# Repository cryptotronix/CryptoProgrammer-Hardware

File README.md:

# Crypto Programmer Hardware

This repo is the hardware files for the Crypto Programmer, a tool that
is hopefully useful for working with the Microchip
CryptoAuthentication Line.

Microchip already makes a useful development git
(https://www.microchip.com/developmenttools/productdetails.aspx?partno=at88ck101sk-mah-xpro),
and the schematics and firmware, but we wanted to "Build our own
Birdfeeder." The intention for this project is to fully Open Source
Hardware, although it doesn't quite meet the definition:
https://www.oshwa.org/definition/

## Overview

The intention of this tool is to expose a scripting-like interface on
a USB-Host that can send the raw byte commands to the part over
I2C. In other words, it is an USB-to-I2C bridge. Most dedicated
USB-to-I2C bridge have a hard-stop of a reasonable number of
bytes. The CryptoAuthentication parts however, send commands in the
few hundred bytes in a continuous I2C frame. Hence, why this tool
exists.

The other use-case for this tool is that you could program the MCU and
then use it to program other CryptoAuthentication parts with the use
of the "extra special button." I often lift CryptoAuthentication parts
from PCBs, drop them in a socket and dump their memory and this tool
should make that easier for me as well.

## Hardware Required

You'll want to attach the USB micro cable to the Crypto Programmer
then attach the plug-side to an appropriate port. I2C lines are on the
right-angle header and you can fly-wire to your heart's content, but
your life will be much easier if you get yourself the AT88CK101 Kit
(https://www.microchip.com/developmenttools/productdetails.aspx?partno=at88ck101sk-mah-xpro)
which comes with a UDFN or SOIC8 socket. The right angle header will
mate with the socket board. This will allow you to test your code
against the Microchip tools, use the CryptoProgammer, and then attach
it to a Microchip development board like a SAMV71.

## Status

Rev A of the Hardware is done and works (we think). We are still
working on the firmware, so once that's in a workable state that will
be released under a BSD license.

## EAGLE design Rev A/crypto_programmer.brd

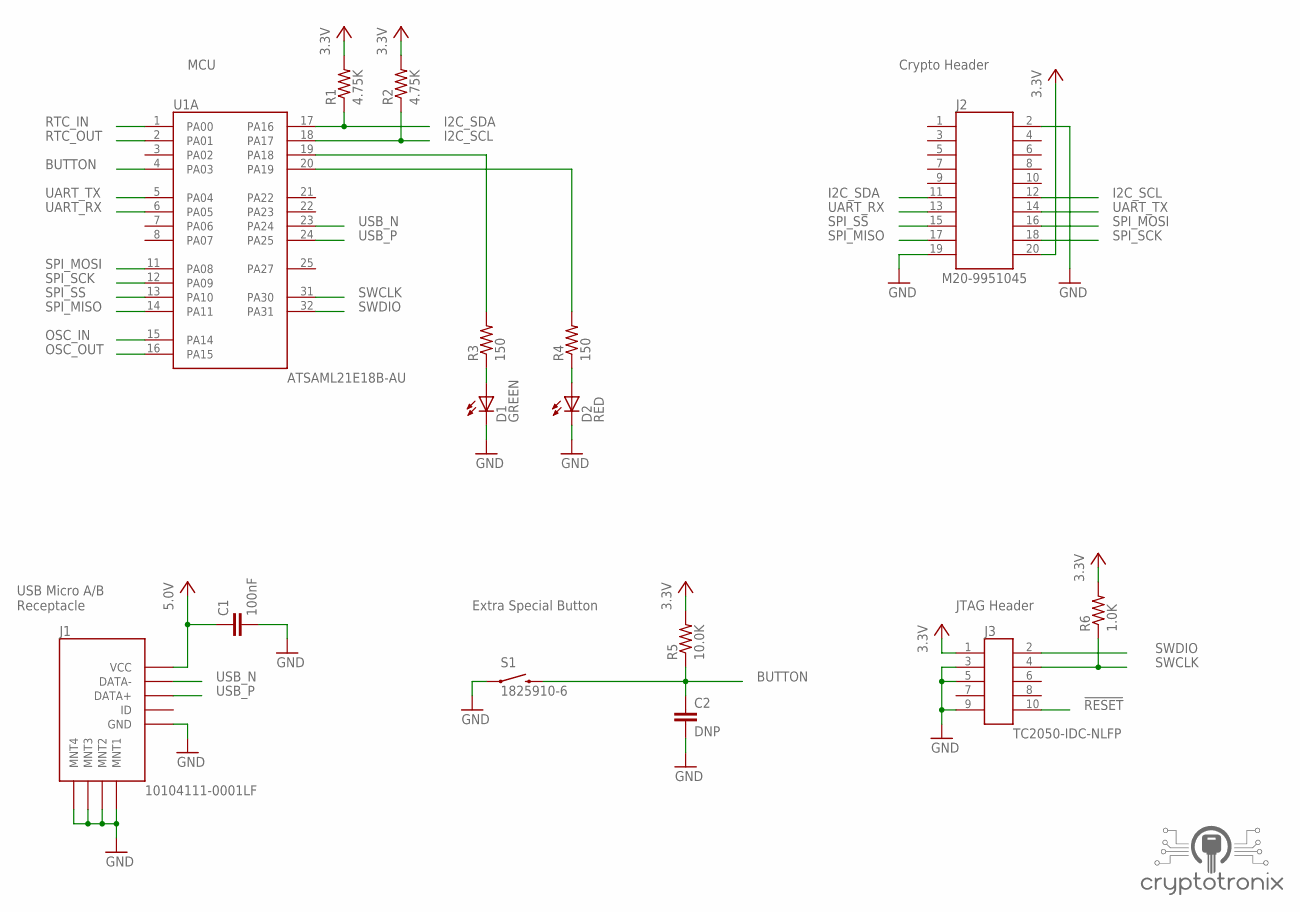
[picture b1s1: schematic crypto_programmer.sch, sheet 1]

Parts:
C1: 100nF; C0603
C2: DNP; C0603
D1: GREEN; 0603
D2: RED; 0603
J1: 10104111-0001LF
J2: M20-9951045
J3: TC2050-IDC-NLFP
LOGO1: CRYPTOTRONIX_LOGO
R1, R2: 4.75K; R0603
R3, R4: 150; R0603
R5: 10.0K; R0603
R6: 1.0K; R0603
S1: 1825910-6; SWITCH-TACT-TH
U1: ATSAML21E18B-AU; ATSAML21E18-AU

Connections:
0V: C1.2, C2.2, D1.C, D2.C, J1.P$5 (GND), J1.P$6 (MNT1), J1.P$7 (MNT2), J1.P$8 (MNT3), J1.P$9 (MNT4), J2.2, J2.19, J3.3, J3.5, J3.9, S1.1; also elsewhere on the board
3.3V: J2.20, J3.1, R1.2, R2.2, R5.2, R6.2; also elsewhere on the board
5.0V: C1.1, J1.P$1 (VCC); also elsewhere on the board
!RESET: J3.10; also elsewhere on the board
BUTTON: C2.1, R5.1, S1.3 (2), U1.4 (PA03)
I2C_SCL: J2.12, R2.1, U1.18 (PA17); also elsewhere on the board
I2C_SDA: J2.11, R1.1, U1.17 (PA16); also elsewhere on the board
unnamed: R4.2, U1.20 (PA19)
unnamed: D2.A, R4.1
unnamed: D1.A, R3.1
unnamed: R3.2, U1.19 (PA18)
OSC_IN: U1.15 (PA14); also elsewhere on the board
OSC_OUT: U1.16 (PA15); also elsewhere on the board
RTC_IN: U1.1 (PA00); also elsewhere on the board
RTC_OUT: U1.2 (PA01); also elsewhere on the board
SPI_MISO: J2.17, U1.14 (PA11)
SPI_MOSI: J2.16, U1.11 (PA08)
SPI_SCK: J2.18, U1.12 (PA09)
SPI_SS: J2.15, U1.13 (PA10)
SWCLK: J3.4, R6.1, U1.31 (PA30)
SWDIO: J3.2, U1.32 (PA31)
UART_RX: J2.13, U1.6 (PA05); also elsewhere on the board
UART_TX: J2.14, U1.5 (PA04); also elsewhere on the board
USB_N: J1.P$2 (DATA-), U1.23 (PA24)
USB_P: J1.P$3 (DATA+), U1.24 (PA25)

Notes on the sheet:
MCU
JTAG Header
Extra Special Button
Crypto Header
USB Micro A/B Receptacle

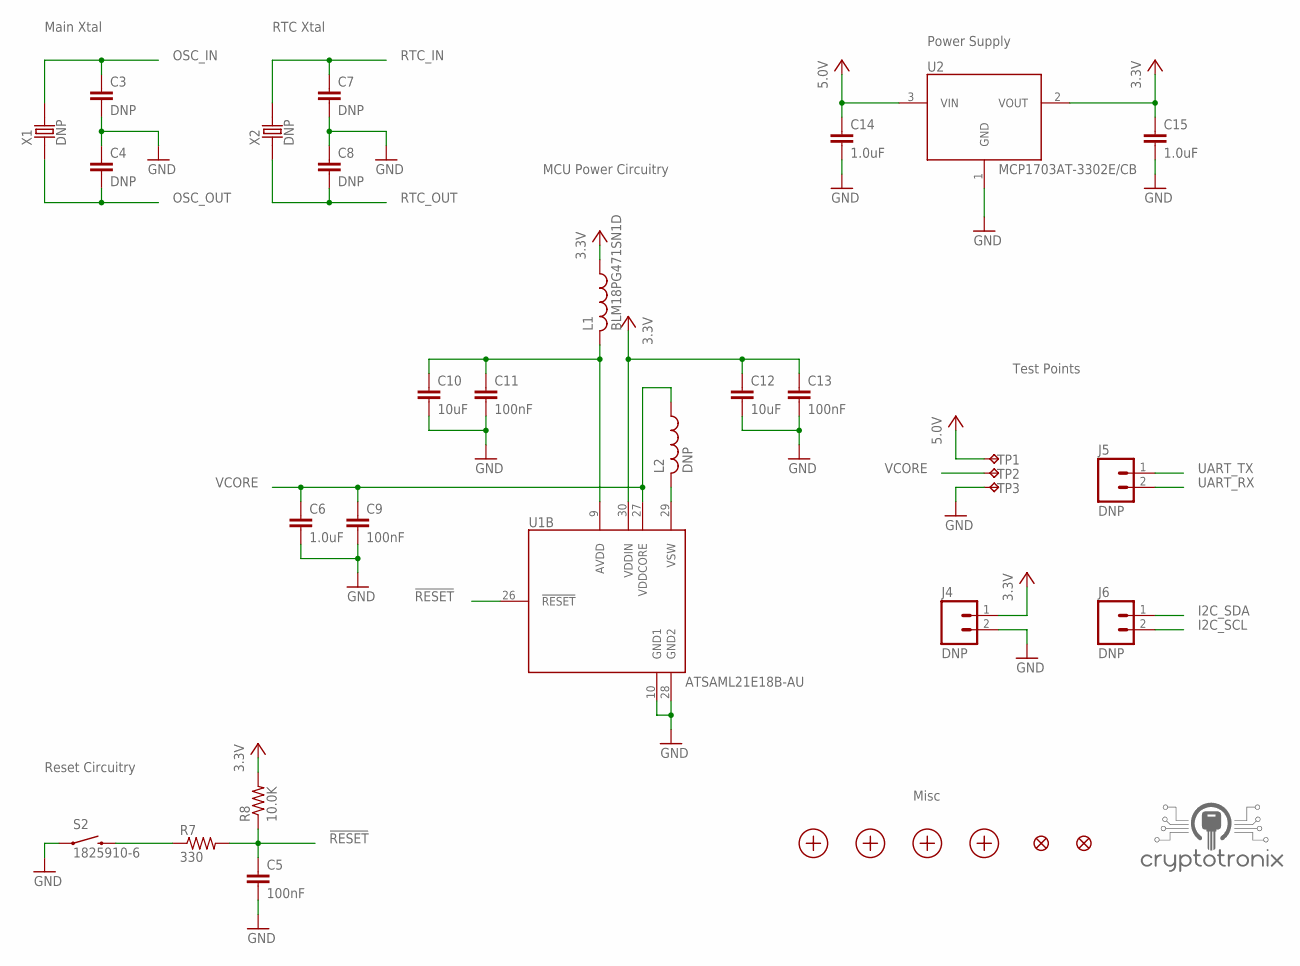
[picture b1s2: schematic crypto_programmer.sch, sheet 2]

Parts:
C3, C4, C7, C8: DNP; C0603
C5, C9, C11, C13: 100nF; C0603
C6, C14, C15: 1.0uF; C0603
C10, C12: 10uF; C0805
FD1, FD2: FIDUCIALUFIDUCIAL; MICRO-FIDUCIAL
J4, J5, J6: DNP; M20-9990246
L1: BLM18PG471SN1D; L0603
L2: DNP; L0603
LOGO2: CRYPTOTRONIX_LOGO
MNT1, MNT2, MNT3, MNT4: MOUNT-HOLE-NO-PLATE4-40; MOUNT-HOLE-NO-PLATE-4-40
R7: 330; R0603
R8: 10.0K; R0603
S2: 1825910-6; SWITCH-TACT-TH
TP1, TP2, TP3: TEST-POINT40MIL; TEST-POINT-40MILL
U1: ATSAML21E18B-AU; ATSAML21E18-AU
U2: MCP1703AT-3302E/CB
X1: DNP; ABL-8.000MHZ-B2
X2: DNP; ABS07AIG-32.768KHZ-9-T

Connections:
0V: C3.2, C4.1, C5.2, C6.2, C7.2, C8.1, C9.2, C10.2, C11.2, C12.2, C13.2, C14.2, C15.2, J4.2, S2.1, TP3.1, U1.10 (GND1), U1.28 (GND2), U2.1 (GND); also elsewhere on the board
3.3V: C12.1, C13.1, C15.1, J4.1, L1.1, R8.2, U1.30 (VDDIN), U2.2 (VOUT); also elsewhere on the board
5.0V: C14.1, TP1.1, U2.3 (VIN); also elsewhere on the board
!RESET: C5.1, R7.2, R8.1, U1.26 (!RESET); also elsewhere on the board
I2C_SCL: J6.2; also elsewhere on the board
I2C_SDA: J6.1; also elsewhere on the board
unnamed: L2.2, U1.29 (VSW)
unnamed: C10.1, C11.1, L1.2, U1.9 (AVDD)
unnamed: R7.1, S2.3 (2)
OSC_IN: C3.1, X1.2; also elsewhere on the board
OSC_OUT: C4.2, X1.1; also elsewhere on the board
RTC_IN: C7.1, X2.2; also elsewhere on the board
RTC_OUT: C8.2, X2.1; also elsewhere on the board
UART_RX: J5.2; also elsewhere on the board
UART_TX: J5.1; also elsewhere on the board
VCORE: C6.1, C9.1, L2.1, TP2.1, U1.27 (VDDCORE)

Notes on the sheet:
MCU Power Circuitry
Reset Circuitry
Test Points
Main Xtal
RTC Xtal
Power Supply
Misc

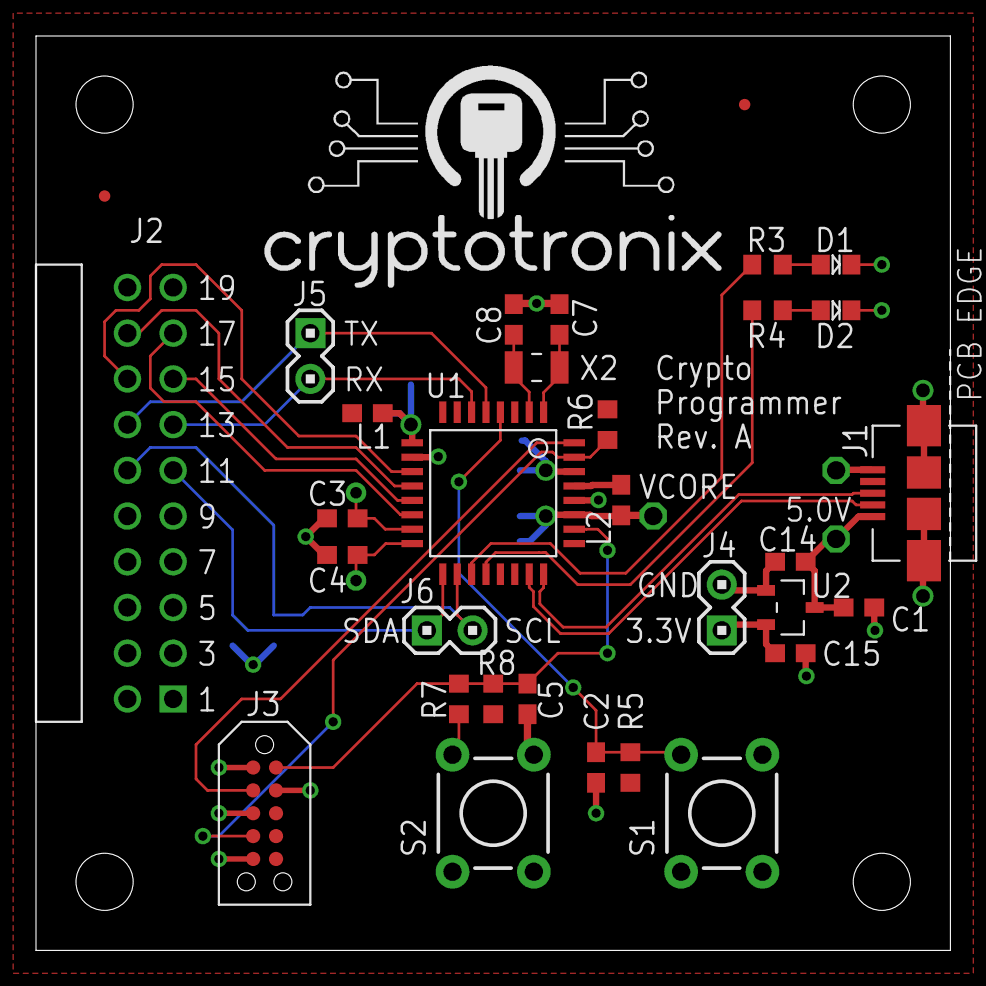
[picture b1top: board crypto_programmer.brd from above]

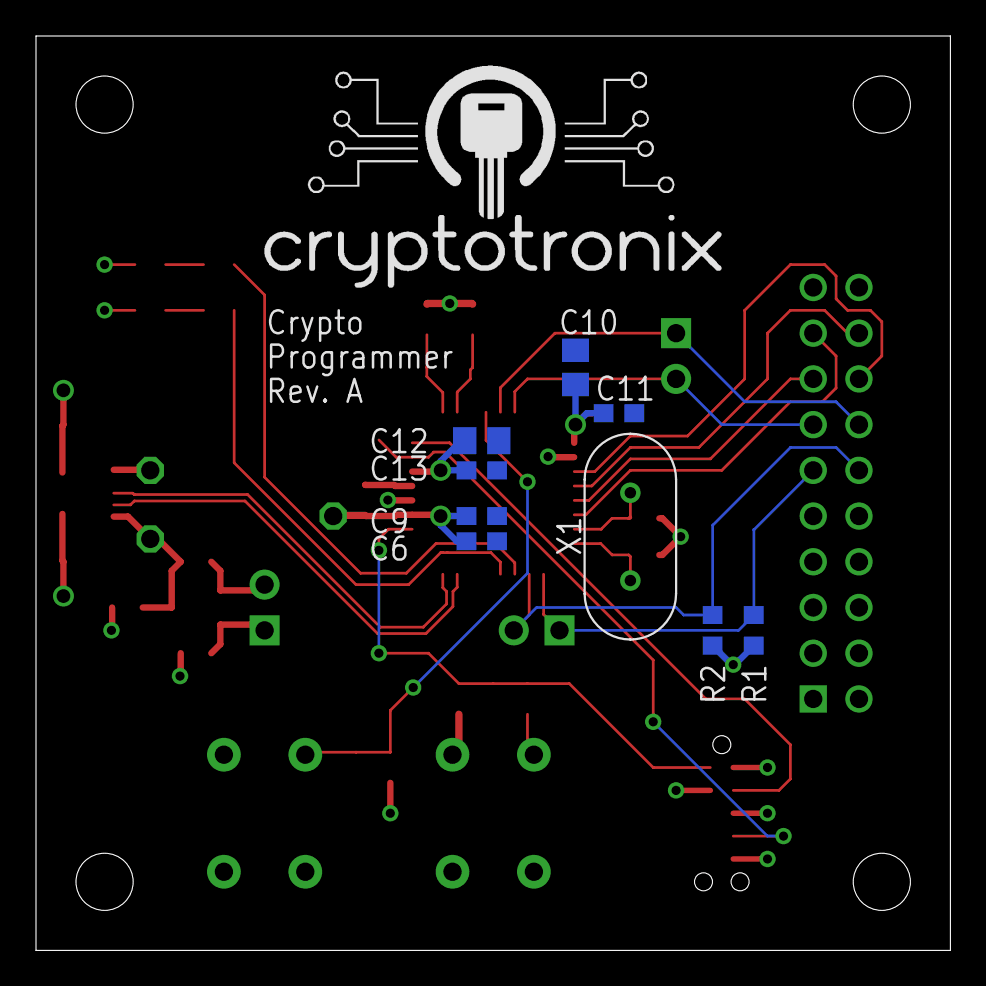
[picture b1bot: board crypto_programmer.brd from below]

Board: 2 copper layers, 50.8 x 50.8 mm, 50 parts (10 on the bottom side), 29 nets.

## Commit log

2017-08-18 Inital commit cont...
2017-08-18 Adding BOM
2017-08-18 Updating BOM 2
2017-08-29 Updating schematics pdf
2017-11-29 updates readme
